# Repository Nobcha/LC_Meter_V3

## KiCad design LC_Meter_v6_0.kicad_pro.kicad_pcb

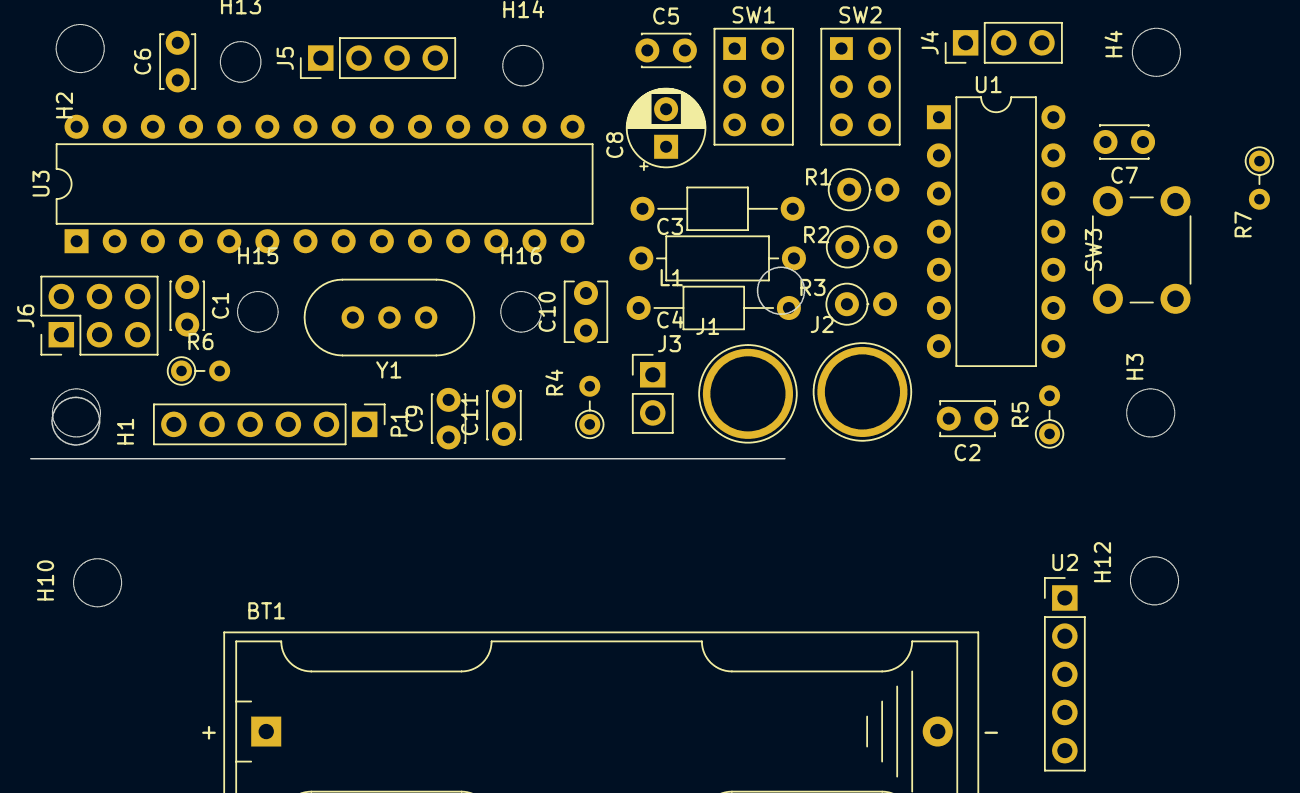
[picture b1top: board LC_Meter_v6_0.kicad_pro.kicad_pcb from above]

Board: 2 copper layers, 50 parts (0 on the bottom side), 24 nets, no tracks yet.

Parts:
BT1: Battery_Cell; BatteryHolder_Keystone_2466_1xAAA
C1, C5, C7: 0.1u; C_Disc_D3.0mm_W2.0mm_P2.50mm
C2, C6: 0.1u; C_Disc_D3.4mm_W2.1mm_P2.50mm
C3: 1000p; C_Axial_L3.8mm_D2.6mm_P10.00mm_Horizontal
C4: 470p; C_Axial_L3.8mm_D2.6mm_P10.00mm_Horizontal
C8: 10u; CP_Radial_D5.0mm_P2.50mm
C9, C11: 20p; C_Disc_D3.0mm_W2.0mm_P2.50mm
C10: 0.1u; C_Disc_D3.8mm_W2.6mm_P2.50mm
H1, H2, H3, H4, H5, H6, H7, H8, H9, H10, H11, H12: MountingHole3.2; MountingHole_3.2mm_M3
H13, H14, H15, H16: MountingHole3; MountingHole_2.7mm_M2.5
J1: Terminal_1; TestPoint_Plated_Hole_D5.0mm
J2: Terminal_2; TestPoint_Plated_Hole_D5.0mm
J3: TEST; PinHeader_1x02_P2.54mm_Vertical
J4: Conn_01x03_Pin; PinHeader_1x03_P2.54mm_Vertical
J5: Conn_i2c LCD; PinHeader_1x04_P2.54mm_Vertical
J6: ICSP; PinHeader_2x03_P2.54mm_Vertical
L1: 22u; L_Axial_L6.6mm_D2.7mm_P10.16mm_Horizontal_Vishay_IM-2
P1: COM; PinHeader_1x06_P2.54mm_Vertical
R1: 1M; R_Axial_DIN0207_L6.3mm_D2.5mm_P2.54mm_Vertical
R2: 5.6k; R_Axial_DIN0207_L6.3mm_D2.5mm_P2.54mm_Vertical
R3: 500k; R_Axial_DIN0207_L6.3mm_D2.5mm_P2.54mm_Vertical
R4, R5, R6, R7: 10k; R_Axial_DIN0204_L3.6mm_D1.6mm_P2.54mm_Vertical
SW1, SW2: SW_DPDT_x2; SW_NKK_G1xJP
SW3: RESET; SW_PUSH_6mm_H4.3mm
U1: 74HCU04; DIP-14_W7.62mm
U2: BAT-CHA; PinHeader_1x05_P2.54mm_Vertical
U3: ATmega328P-PU; DIP-28_W7.62mm
Y1: 16MHz; Crystal_HC49-U-3Pin_Vertical

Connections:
+5V: C1.1, C7.1, C8.1, J4.2, J4.3, J5.1, J6.6, R4.2, R5.2, R7.1, U1.14 (VCC), U2.1 (V-OUT)
/0(Rx): P1.3, U3.2 (PD0)
/1(Tx): P1.2, U3.3 (PD1)
/5(**): R3.1, U1.8, U3.11 (PD5)
/6(**): R4.1, SW2.1 (A), U3.12 (PD6)
/7: R5.1, SW1.6 (C), U3.13 (PD7)
/11(**/MOSI): J6.5, U3.17 (PB3)
/12(MISO): J6.1, U3.18 (PB4)
/13(SCK): J6.2, U3.19 (PB5)
/DTR: C10.2, P1.1
/Reset: C10.1, J6.3, R6.2, R7.2, SW3.2, U3.1 (~RESET/PC6)
GND: BT1.2 (-), C1.2, C4.1, C5.1, C6.1, C7.2, C8.2, C9.2, C11.2, J2.1, J3.2, J4.1, J5.4, J6.4, P1.5, P1.6, SW1.5 (B), SW2.2 (B), SW2.5 (B), SW3.1, U1.1, U1.3, U1.5, U1.7 (GND), U2.2 (GND), U2.4 (GND), U3.8 (GND), U3.22 (GND), Y1.2
unnamed: BT1.1 (+), U2.3 (BAT-IN)
unnamed: C2.2, R1.2, U1.13
unnamed: J1.1, J3.1, SW1.2 (B)
unnamed: R1.1, U1.11, U1.12
unnamed: R2.1, R3.2, U1.9, U1.10
unnamed: C2.1, C3.2, C4.2, L1.2, R2.2, SW1.1 (A)
unnamed: L1.1, SW1.3 (C), SW1.4 (A)
unnamed: C3.1, SW2.4 (A)
unnamed: C5.2, U3.21 (AREF)
unnamed: C11.1, U3.9 (XTAL1/PB6), Y1.3
unnamed: C9.1, U3.10 (XTAL2/PB7), Y1.1
VCC: C6.2, P1.4, R6.1, U3.7 (VCC), U3.20 (AVCC)

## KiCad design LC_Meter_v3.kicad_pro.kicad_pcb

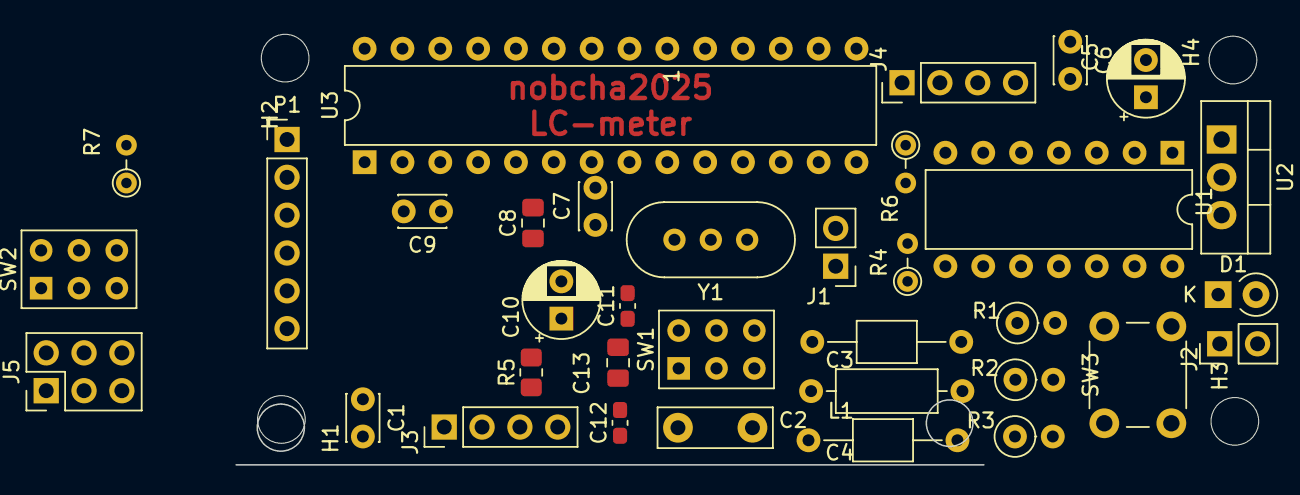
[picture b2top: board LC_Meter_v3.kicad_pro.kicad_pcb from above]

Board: 2 copper layers, 47 parts (0 on the bottom side), 26 nets, no tracks yet.

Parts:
C1, C6, C7, C9: 0.1u; C_Disc_D3.0mm_W2.0mm_P2.50mm
C2: 0.1u; C_Disc_D7.5mm_W2.5mm_P5.00mm
C3: 1000p; C_Axial_L3.8mm_D2.6mm_P10.00mm_Horizontal
C4: 470p; C_Axial_L3.8mm_D2.6mm_P10.00mm_Horizontal
C5, C10: 10u; CP_Radial_D5.0mm_P2.50mm
C8, C13: 0.1u; C_0805_2012Metric_Pad1.18x1.45mm_HandSolder
C11, C12: 20p; C_0603_1608Metric_Pad1.08x0.95mm_HandSolder
D1: 1S1588; D_A-405_P2.54mm_Vertical_KathodeUp
H1, H2, H3, H4, H5, H6, H7, H8, H9, H10, H11, H12: MountingHole3.2; MountingHole_3.2mm_M3
J1: TEST; PinHeader_1x02_P2.54mm_Vertical
J2: Conn_DC-IN; PinHeader_1x02_P2.54mm_Vertical
J3: DC_SEL; PinHeader_1x04_P2.54mm_Vertical
J4: Conn_i2c LCD; PinHeader_1x04_P2.54mm_Vertical
J5: ICSP; PinHeader_2x03_P2.54mm_Vertical
L1: 22u; L_Axial_L6.6mm_D2.7mm_P10.16mm_Horizontal_Vishay_IM-2
P1: COM; PinHeader_1x06_P2.54mm_Vertical
R1: 1M; R_Axial_DIN0207_L6.3mm_D2.5mm_P2.54mm_Vertical
R2: 5.6k; R_Axial_DIN0207_L6.3mm_D2.5mm_P2.54mm_Vertical
R3: 500k; R_Axial_DIN0207_L6.3mm_D2.5mm_P2.54mm_Vertical
R4, R6, R7: 10k; R_Axial_DIN0204_L3.6mm_D1.6mm_P2.54mm_Vertical
R5: 10k; R_0805_2012Metric_Pad1.20x1.40mm_HandSolder
SW1, SW2: SW_DPDT_x2; SW_NKK_G1xJP
SW3: RESET; SW_PUSH_6mm_H4.3mm
U1: 74HCU04; DIP-14_W7.62mm
U2: LM78M05_TO220; TO-220-3_Vertical
U3: ATmega328P-PU; DIP-28_W7.62mm
Y1: 16MHz; Crystal_HC49-U-3Pin_Vertical

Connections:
+5V: C1.1, J3.3, J4.1, J5.6, R4.2, R6.1, R7.2, U1.14 (VCC)
/0(Rx): P1.3, U3.2 (PD0)
/1(Tx): P1.2, U3.3 (PD1)
/5(**): R3.1, U1.8, U3.11 (PD5)
/6(**): R7.1, SW2.1 (A), U3.12 (PD6)
/7: R4.1, SW1.6 (C), U3.13 (PD7)
/11(**/MOSI): J5.5, U3.17 (PB3)
/12(MISO): J5.1, U3.18 (PB4)
/13(SCK): J5.2, U3.19 (PB5)
/DTR: C13.2, P1.1
/Reset: C13.1, J5.3, R5.2, R6.2, SW3.2, U3.1 (~RESET/PC6)
GND: C1.2, C4.1, C5.2, C6.2, C7.1, C8.1, C9.2, C10.2, C11.2, C12.2, J1.2, J2.2, J4.4, J5.4, P1.5, P1.6, SW1.5 (B), SW2.2 (B), SW2.5 (B), SW3.1, U1.1, U1.3, U1.5, U1.7 (GND), U2.2 (GND), U3.8 (GND), U3.22 (GND), Y1.2
unnamed: C2.2, R1.2, U1.13
unnamed: D1.2 (A), J2.1
unnamed: C5.1, C6.1, D1.1 (K), J3.1, U2.1 (VI)
unnamed: J1.1, SW1.2 (B)
unnamed: C9.1, C10.1, J3.4, U2.3 (VO)
unnamed: R1.1, U1.11, U1.12
unnamed: R2.1, R3.2, U1.9, U1.10
unnamed: C2.1, C3.2, C4.2, L1.2, R2.2, SW1.1 (A)
unnamed: L1.1, SW1.3 (C), SW1.4 (A)
unnamed: C3.1, SW2.4 (A)
unnamed: C7.2, U3.21 (AREF)
unnamed: C12.1, U3.9 (XTAL1/PB6), Y1.3
unnamed: C11.1, U3.10 (XTAL2/PB7), Y1.1
VCC: C8.2, P1.4, R5.1, U3.7 (VCC), U3.20 (AVCC)

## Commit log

2025-06-26 LCM V3 PRO@KiCAD
    KiCAD 7.0 pro file for LC meter
2025-06-26 KiCAD 7.0 pcb file for LC meter
2025-06-26 KiCAD 7.0 sch file for LC meter
2025-06-26 Advanced design V1
2025-06-27 OLED ASSY tremanifactured
    3.3V AVR, pull up, SSD1306 connection
2025-06-29 Updated pcb file
2025-06-30 Add the updated files
    3 kinds of PCB are combined.
